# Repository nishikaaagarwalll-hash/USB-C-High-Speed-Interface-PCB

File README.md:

# USB-C High-Speed Interface & Power Management PCB

A USB-C interface PCB designed using **KiCad 9.0**, focusing on USB 2.0 connectivity, ESD protection, power regulation, and practical PCB design workflows.

## Project Overview

This project focuses on designing a USB Type-C interface board that provides USB 2.0 data connectivity and a regulated power supply for a USB-to-UART interface.

The design combines USB-C connector interfacing, USB data-line protection, power management, and PCB layout considerations in a structured hardware design project.

**Project status:** PCB design uploaded to GitHub for educational and portfolio purposes. Physical fabrication and hardware testing have not been performed.

## Objectives

* Design a USB Type-C receptacle interface for USB 2.0 data communication.
* Incorporate ESD protection for USB data lines.
* Implement USB-C CC1/CC2 configuration using appropriate pull-down resistors.
* Design a protected 5 V power input and 3.3 V regulation stage.
* Develop a schematic and PCB layout using KiCad.
* Practice PCB design-rule checking, electrical-rule checking, and hardware documentation.

## Key Features

* USB Type-C connector interface
* USB 2.0 D+ and D− signal routing
* USBLC6-2SC6 ESD protection
* CH340C USB-to-UART interface
* AP2112K-3.3 voltage regulator
* Protected VBUS power input
* CC1/CC2 pull-down configuration
* UART TX/RX header interface
* PCB layout and design validation using KiCad

## Tools Used

| Tool      | Purpose                                 |
| --------- | --------------------------------------- |
| KiCad 9.0 | Schematic capture and PCB layout        |
| LTspice   | Optional future circuit simulation      |
| Python    | Optional future analysis and automation |

## Hardware Design

### 1. USB Type-C Interface

The USB-C receptacle provides the physical connection for USB communication and power input. The CC1 and CC2 pins use configuration pull-down resistors intended for a USB device/sink interface.

### 2. USB Data-Line Protection

The USBLC6-2SC6 is included to provide electrostatic discharge protection for the USB data lines.

### 3. USB-to-UART Conversion

The CH340C provides a USB-to-UART bridge, allowing USB communication to be converted into serial TX/RX signals.

### 4. Power Management

The design includes a protected VBUS power path and an AP2112K-3.3 regulator intended to provide a 3.3 V supply.

The final power performance depends on component selection, circuit implementation, loading, and validation.

### 5. PCB Layout

The PCB is designed in KiCad with attention to component placement, ground return paths, routing, clearances, and USB differential-pair layout considerations.

A four-layer stackup and controlled-impedance routing are design goals that require appropriate stackup specifications and impedance verification before fabrication.

## Project Structure

```text
USB-C-High-Speed-Interface-PCB/
├── 01_Design and manufacturing/
├── 06_Documention
├── 07_Images/
├── README.md
├── USB_C_Interface.kicad_pro
├── USB_C_Interface.kicad_sch
└── USB_C_Interface.kicad_pcb
```

The folder contents may be expanded as supporting documentation, calculations, and design images are added.

## Design Validation

The design has been checked using KiCad's Electrical Rules Checker (ERC) and Design Rules Checker (DRC).

* **ERC errors:** 0 reported
* **DRC errors:** 0 reported
* **Unconnected items:** 0 reported

These results reflect the checks performed on the current design at the time of validation. They do not independently establish electrical performance, USB signal integrity, controlled impedance, or physical hardware functionality.

## Limitations

* USB signal integrity and differential impedance have not been established through physical measurements.
* Power regulation performance has not been validated under real load conditions.
* Connector footprint dimensions and fabrication requirements should be rechecked against the selected manufacturer's documentation before manufacturing.

## Future Improvements

* Verify all footprints and pin mappings against manufacturer datasheets.
* Document the intended PCB stackup and obtain impedance calculations from suitable tools or the fabricator.
* Perform appropriate circuit simulations and document genuine results.
* Review USB routing and return paths for signal integrity.
* Generate and review Gerber, drill, and bill-of-materials outputs.
* Fabricate a prototype and perform electrical and functional tests.

## Learning Outcomes

This project provides practical experience in:

* Electronic schematic design
* USB Type-C interface fundamentals
* USB 2.0 data-line protection
* Power regulation and decoupling
* PCB layout and routing
* KiCad ERC/DRC workflows
* Engineering documentation and version control using GitHub

## Disclaimer

This is an educational PCB design project. All validation statements refer only to the design checks explicitly performed. No claim of USB certification, measured signal integrity, manufacturing readiness, or hardware functionality is made.

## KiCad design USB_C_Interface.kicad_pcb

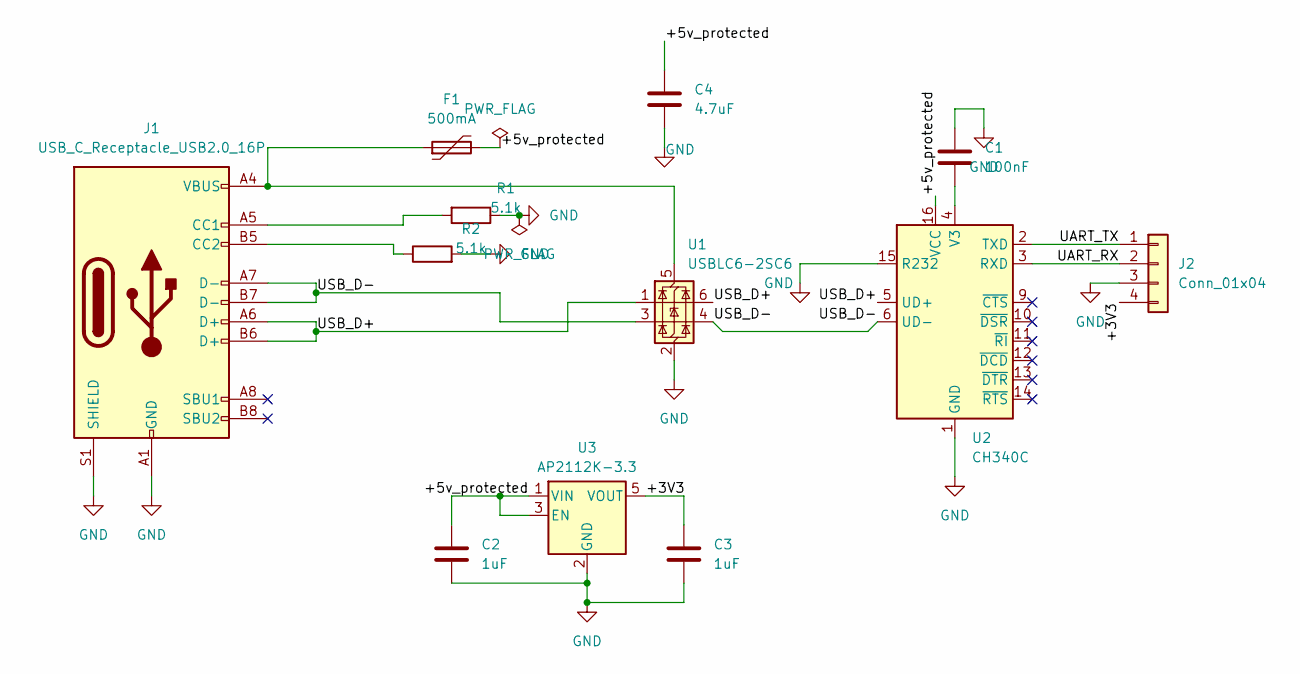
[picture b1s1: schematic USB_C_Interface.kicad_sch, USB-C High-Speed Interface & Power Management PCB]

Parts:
C1: 100nF; C_0603_1608Metric
C2, C3: 1uF; C_0603_1608Metric
C4: 4.7uF; C_0603_1608Metric
F1: 500mA; Fuse_1206_3216Metric
J1: USB_C_Receptacle_USB2.0_16P; USB_C_Receptacle_GCT_USB4105-xx-A_16P_TopMnt_Horizontal
J2: Conn_01x04; PinHeader_1x04_P2.54mm_Vertical
R1, R2: 5.1k; R_0603_1608Metric
U1: USBLC6-2SC6; SOT-23-6
U2: CH340C; SOIC-16_3.9x9.9mm_P1.27mm
U3: AP2112K-3.3; SOT-23-5

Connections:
/+3V3: C3.1, J2.4, U3.5 (VOUT)
/+5v_protected: C2.1, C4.1, F1.2, U2.16 (VCC), U3.1 (VIN), U3.3 (EN)
/UART_RX: J2.2, U2.3 (RXD)
/UART_TX: J2.1, U2.2 (TXD)
/USB_D+: J1.A6 (D+), J1.B6 (D+), U1.1 (I/O1), U1.6 (I/O1), U2.5 (UD+)
/USB_D-: J1.A7 (D-), J1.B7 (D-), U1.3 (I/O2), U1.4 (I/O2), U2.6 (UD-)
GND: C1.1, C2.2, C3.2, C4.2, J1.A1 (GND), J1.A12 (GND), J1.B1 (GND), J1.B12 (GND), J1.S1 (SHIELD), J2.3, R1.1, R2.2, U1.2 (GND), U2.1 (GND), U2.15 (R232), U3.2 (GND)
unnamed: J1.A5 (CC1), R1.2
unnamed: J1.B5 (CC2), R2.1
unnamed: F1.1, J1.A4 (VBUS), J1.A9 (VBUS), J1.B4 (VBUS), J1.B9 (VBUS), U1.5 (VBUS)
unnamed: C1.2, U2.4 (V3)

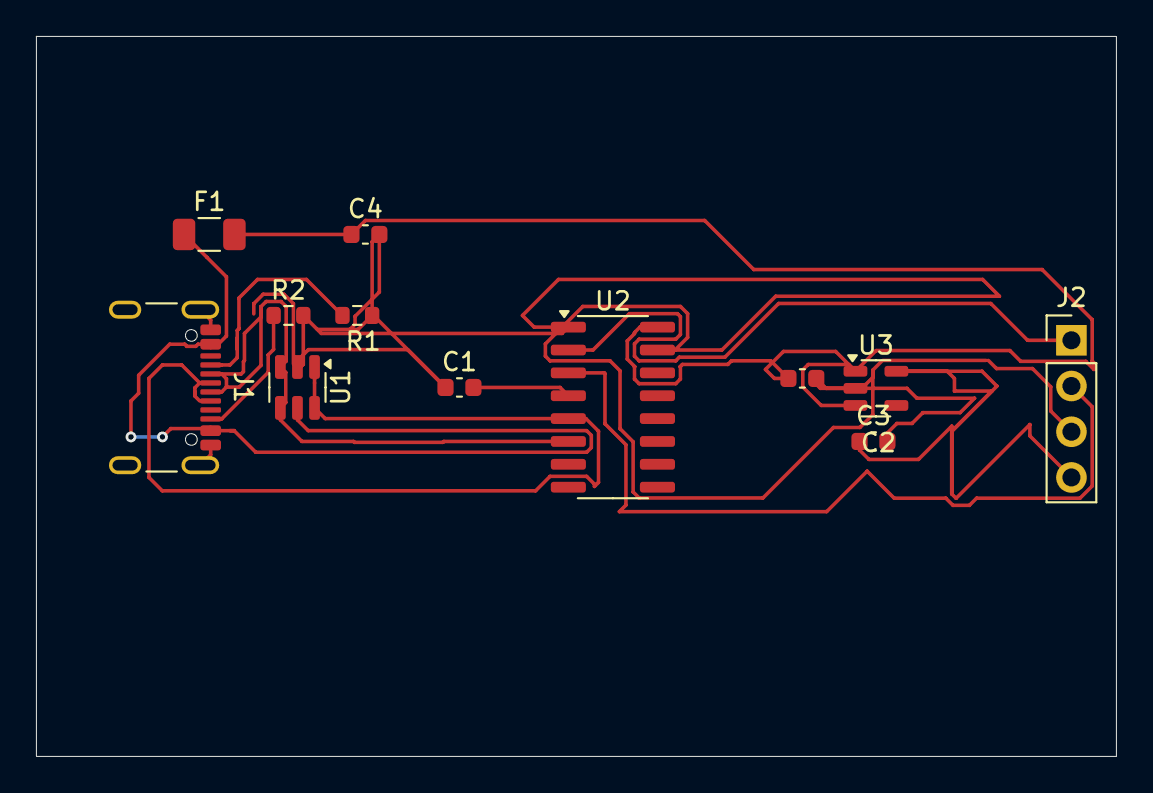
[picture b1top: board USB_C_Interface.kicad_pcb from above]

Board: 4 copper layers, 60.0 x 40.0 mm, 12 parts (0 on the bottom side), 11 nets.

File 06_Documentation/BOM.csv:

"Id";"Designator";"Footprint";"Quantity";"Designation";"Supplier and ref";
1;"U1";"SOT-23-6";1;"USBLC6-2SC6";;;
2;"R1,R2";"R_0603_1608Metric";2;"5.1k";;;
3;"C4";"C_0603_1608Metric";1;"4.7uF";;;
4;"C1";"C_0603_1608Metric";1;"100nF";;;
5;"J2";"PinHeader_1x04_P2.54mm_Vertical";1;"Conn_01x04";;;
6;"U3";"SOT-23-5";1;"AP2112K-3.3";;;
7;"C2,C3";"C_0603_1608Metric";2;"1uF";;;
8;"U2";"SOIC-16_3.9x9.9mm_P1.27mm";1;"CH340C";;;
9;"F1";"Fuse_1206_3216Metric";1;"500mA";;;
10;"J1";"USB_C_Receptacle_GCT_USB4105-xx-A_16P_TopMnt_Horizontal";1;"USB_C_Receptacle_USB2.0_16P";;;
